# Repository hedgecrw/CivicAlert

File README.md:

# CivicAlert
Software, Firmware, and Hardware Design for the CivicAlert Gunshot Locator Project

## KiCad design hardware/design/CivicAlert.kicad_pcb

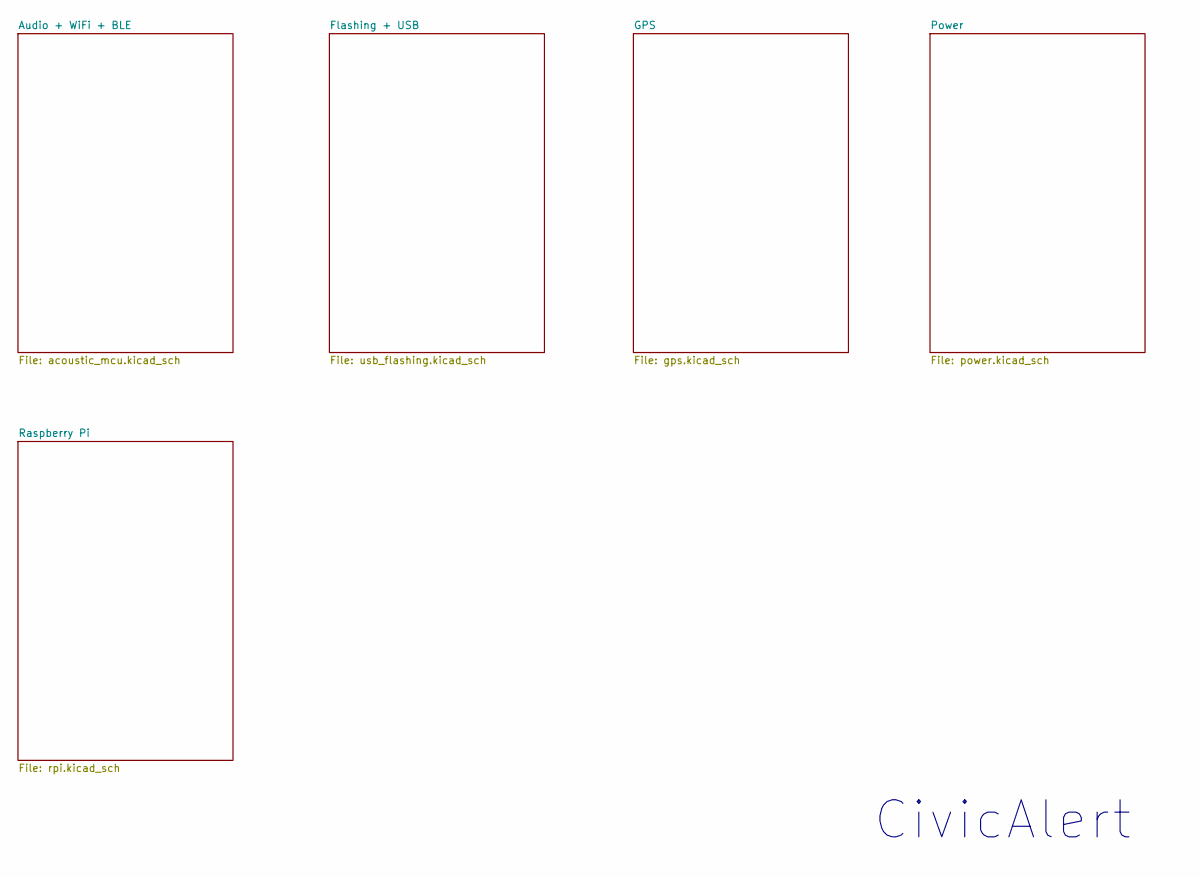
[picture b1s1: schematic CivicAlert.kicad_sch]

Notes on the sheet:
CivicAlert

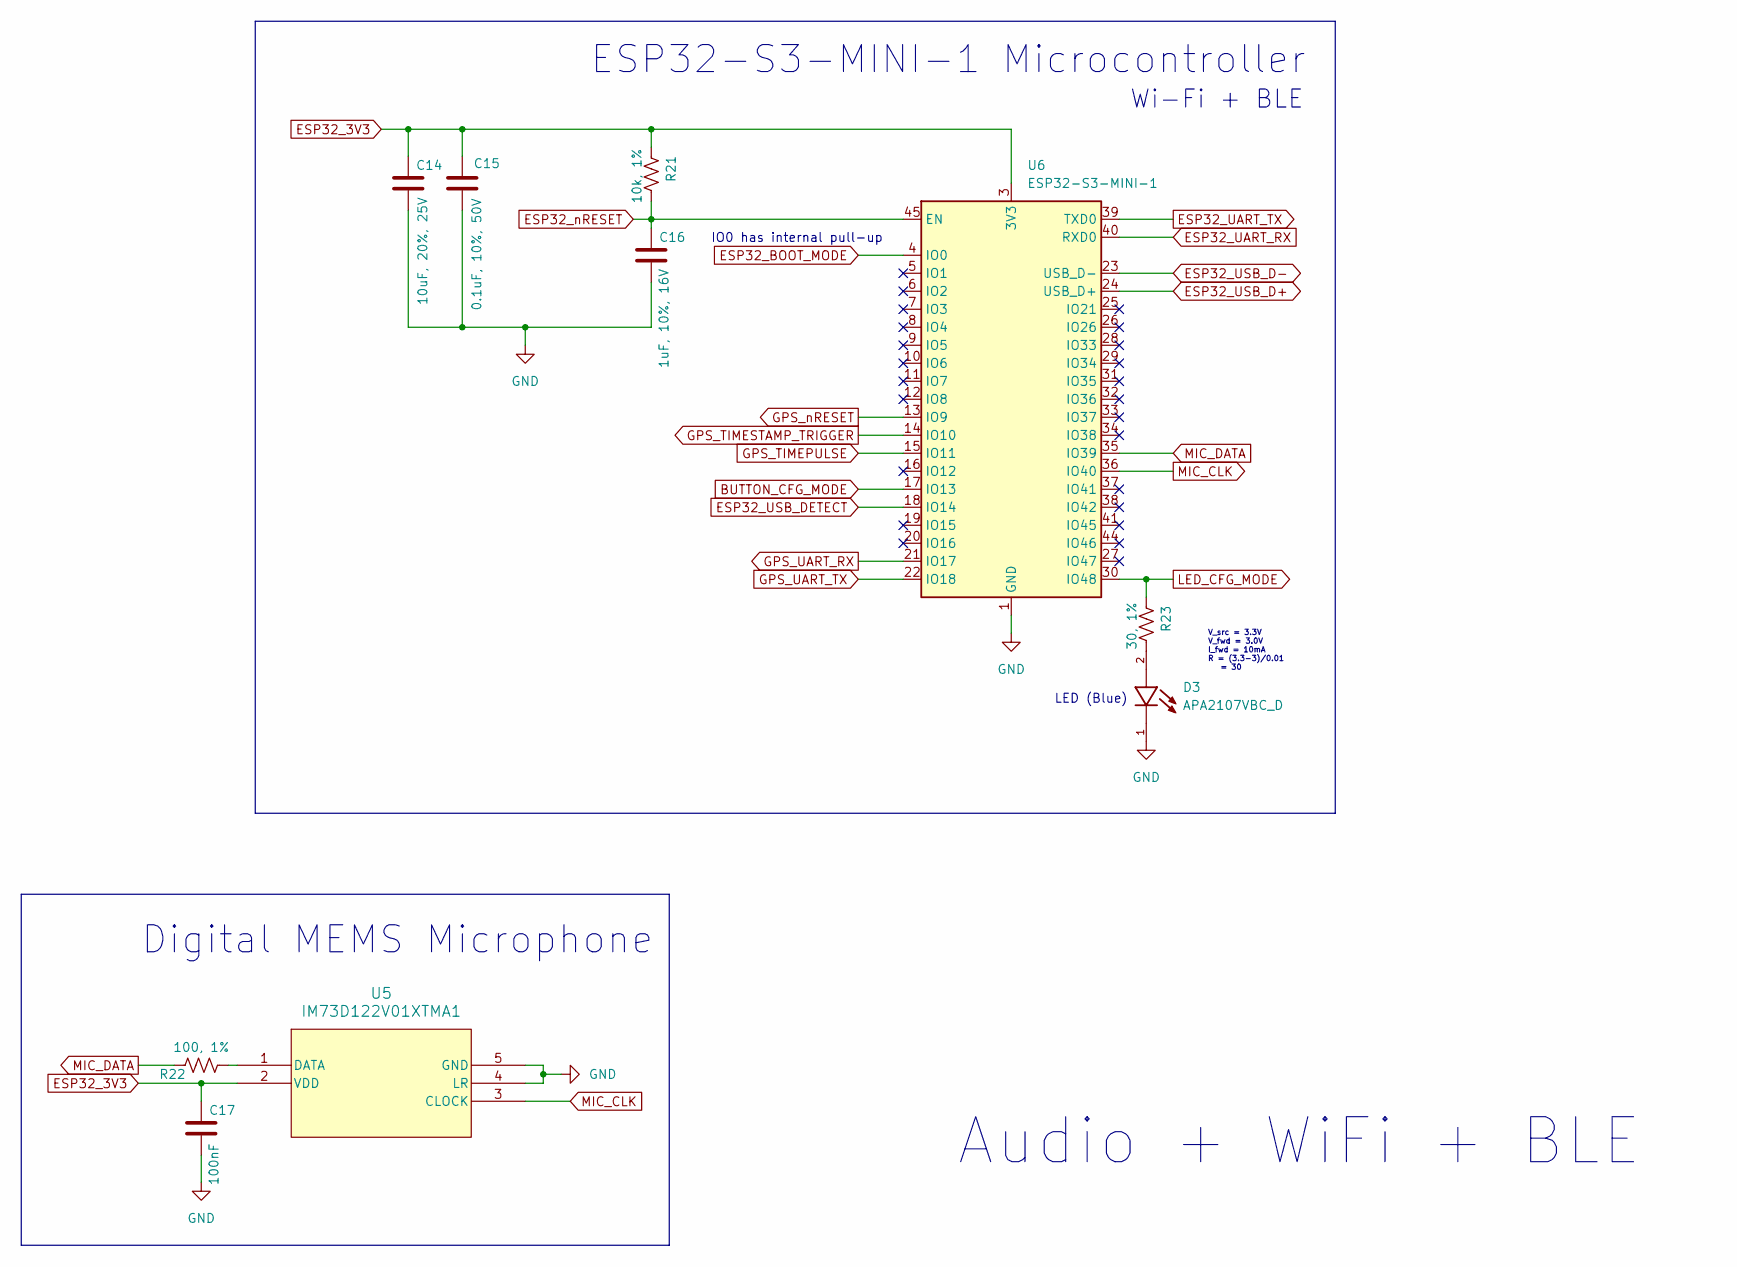
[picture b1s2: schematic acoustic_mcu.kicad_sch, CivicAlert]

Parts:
C14: 10uF, 20%, 25V; C_0805_2012Metric
C15: 0.1uF, 10%, 50V; C_0805_2012Metric
C16: 1uF, 10%, 16V; C_0805_2012Metric
C17: 100nF; C_0805_2012Metric
D3: APA2107VBC_D; LED_APA2107VBC_D; PARTREV V.5B
R21: 10k, 1%; R_0805_2012Metric
R22: 100, 1%; R_0805_2012Metric
R23: 30, 1%; R_0805_2012Metric
U5: IM73D122V01XTMA1; PG-LLGA-5-2_INF
U6: ESP32-S3-MINI-1; ESP32-S2-MINI-1

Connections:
BUTTON_CFG_MODE: U6.17 (IO13); also elsewhere on the board
ESP32_3V3: C14.1, C15.1, C17.1, R21.1, U5.2 (VDD), U6.3 (3V3); also elsewhere on the board
ESP32_BOOT_MODE: U6.4 (IO0); also elsewhere on the board
ESP32_UART_RX: U6.40 (RXD0); also elsewhere on the board
ESP32_UART_TX: U6.39 (TXD0); also elsewhere on the board
ESP32_USB_D+: U6.24 (USB_D+); also elsewhere on the board
ESP32_USB_D-: U6.23 (USB_D-); also elsewhere on the board
ESP32_USB_DETECT: U6.18 (IO14); also elsewhere on the board
ESP32_nRESET: C16.1, R21.2, U6.45 (EN); also elsewhere on the board
GND: C14.2, C15.2, C16.2, C17.2, D3.1, U5.4 (LR), U5.5 (GND), U6.1 (GND), U6.2 (GND), U6.42 (GND), U6.43 (GND), U6.46 (GND), U6.47 (GND), U6.48 (GND), U6.49 (GND), U6.50 (GND), U6.51 (GND), U6.52 (GND), U6.53 (GND), U6.54 (GND), U6.55 (GND), U6.56 (GND), U6.57 (GND), U6.58 (GND), U6.59 (GND), U6.60 (GND), U6.61 (GND), U6.62 (GND), U6.63 (GND), U6.64 (GND), U6.65 (GND); also elsewhere on the board
GPS_TIMEPULSE: U6.15 (IO11); also elsewhere on the board
GPS_TIMESTAMP_TRIGGER: U6.14 (IO10); also elsewhere on the board
GPS_UART_RX: U6.21 (IO17); also elsewhere on the board
GPS_UART_TX: U6.22 (IO18); also elsewhere on the board
GPS_nRESET: U6.13 (IO9); also elsewhere on the board
LED_CFG_MODE: R23.1, U6.30 (IO48)
MIC_CLK: U5.3 (CLOCK), U6.36 (IO40)
MIC_DATA: R22.2, U6.35 (IO39)
unnamed: D3.2, R23.2
unnamed: R22.1, U5.1 (DATA)

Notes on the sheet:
Digital MEMS Microphone
Audio + WiFi + BLE
ESP32-S3-MINI-1 Microcontroller
Wi-Fi + BLE
LED (Blue)
V_src = 3.3V V_fwd = 3.0V I_fwd = 10mA R = (3.3-3)/0.01 = 30
IO0 has internal pull-up

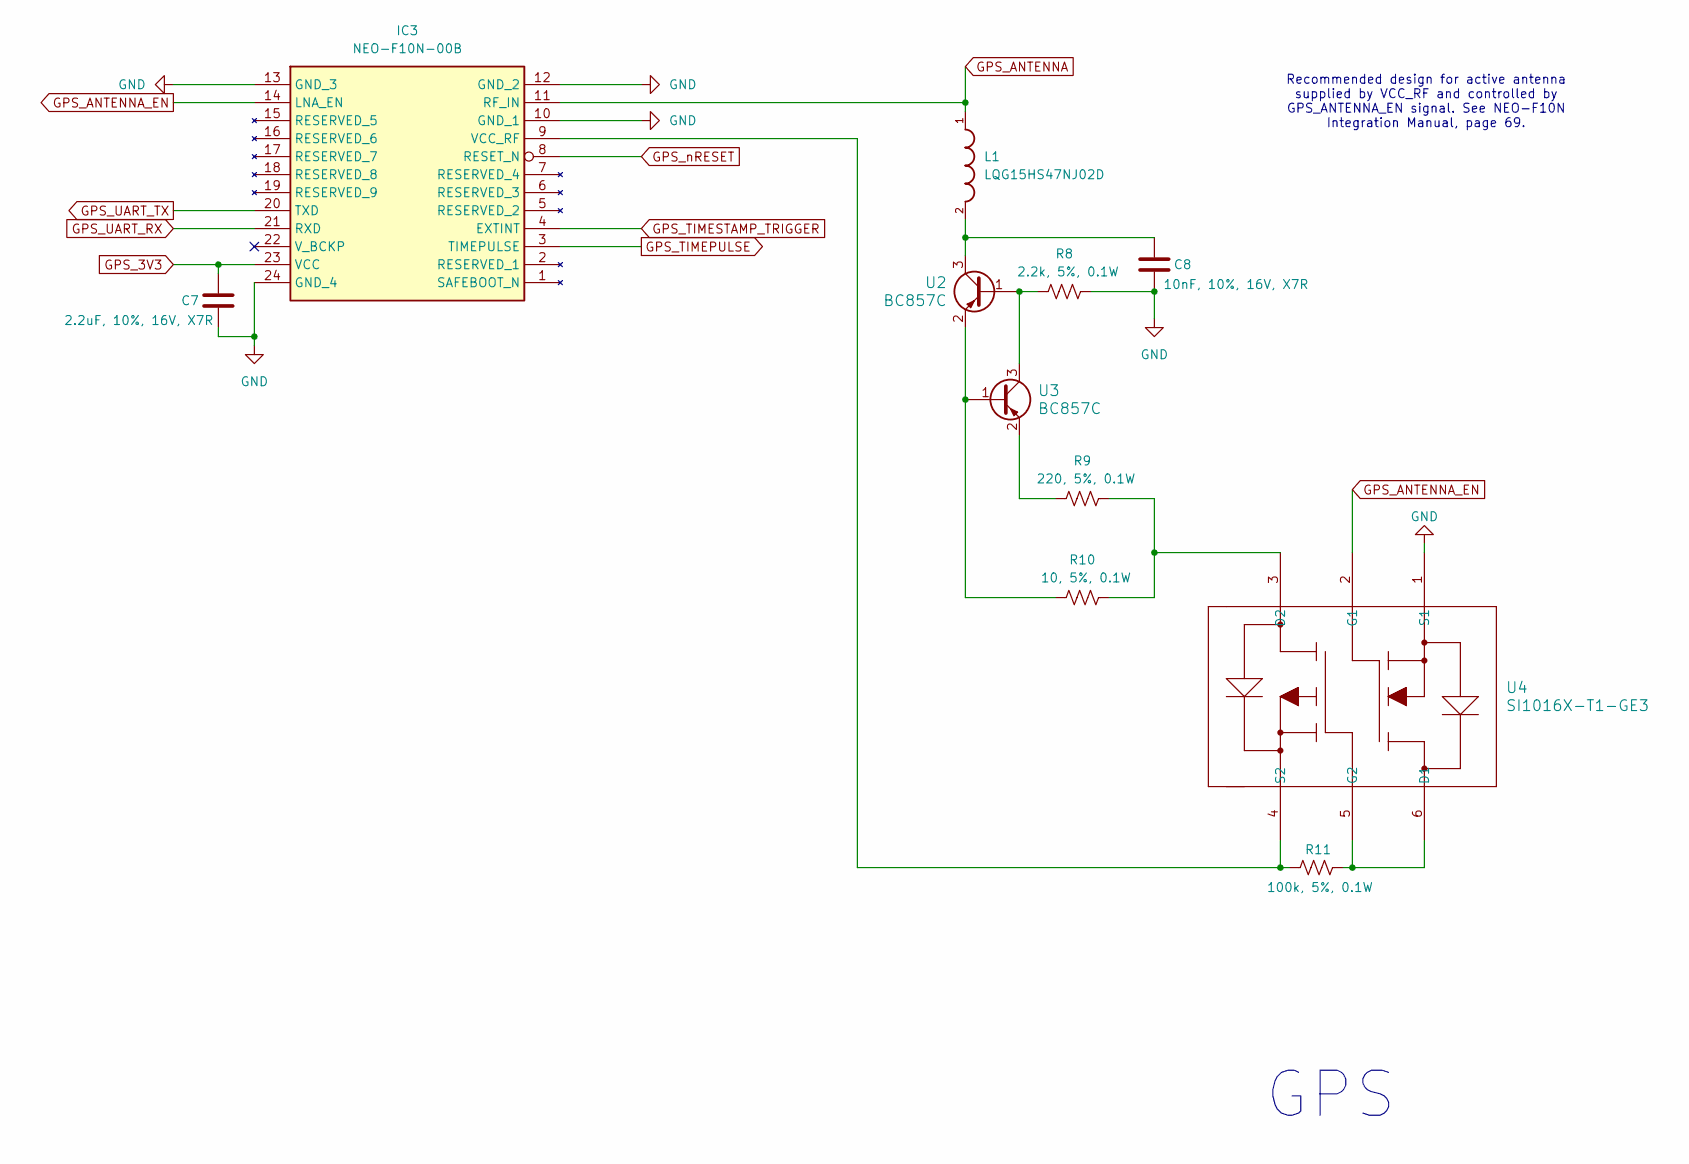
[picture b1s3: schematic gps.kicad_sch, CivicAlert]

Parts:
C7: 2.2uF, 10%, 16V, X7R; C_0805_2012Metric
C8: 10nF, 10%, 16V, X7R; C_0805_2012Metric
IC3: NEO-F10N-00B; NEOF10N00B; Mouser Part Number 377-NEO-F10N-00B
L1: LQG15HS47NJ02D; INDC1005X55N
R8: 2.2k, 5%, 0.1W; R_0805_2012Metric
R9: 220, 5%, 0.1W; R_0805_2012Metric
R10: 10, 5%, 0.1W; R_0805_2012Metric
R11: 100k, 5%, 0.1W; R_0805_2012Metric
U2, U3: BC857C; SOT-23
U4: SI1016X-T1-GE3; SOT_X-T1-GE3_VIS

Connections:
GND: C7.2, C8.2, IC3.10 (GND_1), IC3.12 (GND_2), IC3.13 (GND_3), IC3.24 (GND_4), R8.1, U4.1 (S1); also elsewhere on the board
GPS_3V3: C7.1, IC3.23 (VCC); also elsewhere on the board
GPS_ANTENNA: IC3.11 (RF_IN), L1.1
GPS_ANTENNA_EN: IC3.14 (LNA_EN), U4.2 (G1)
GPS_TIMEPULSE: IC3.3 (TIMEPULSE); also elsewhere on the board
GPS_TIMESTAMP_TRIGGER: IC3.4 (EXTINT); also elsewhere on the board
GPS_UART_RX: IC3.21 (RXD); also elsewhere on the board
GPS_UART_TX: IC3.20 (TXD); also elsewhere on the board
GPS_nRESET: IC3.8 (RESET_N); also elsewhere on the board
unnamed: IC3.9 (VCC_RF), R11.2, U4.4 (S2)
unnamed: R8.2, U2.1 (B), U3.3 (C)
unnamed: C8.1, L1.2, U2.3 (C)
unnamed: R10.2, U2.2 (E), U3.1 (B)
unnamed: R9.2, U3.2 (E)
unnamed: R11.1, U4.5 (G2), U4.6 (D1)
unnamed: R9.1, R10.1, U4.3 (D2)

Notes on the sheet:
GPS
Recommended design for active antenna supplied by VCC_RF and controlled by GPS_ANTENNA_EN signal. See NEO-F10N Integration Manual, page 69.

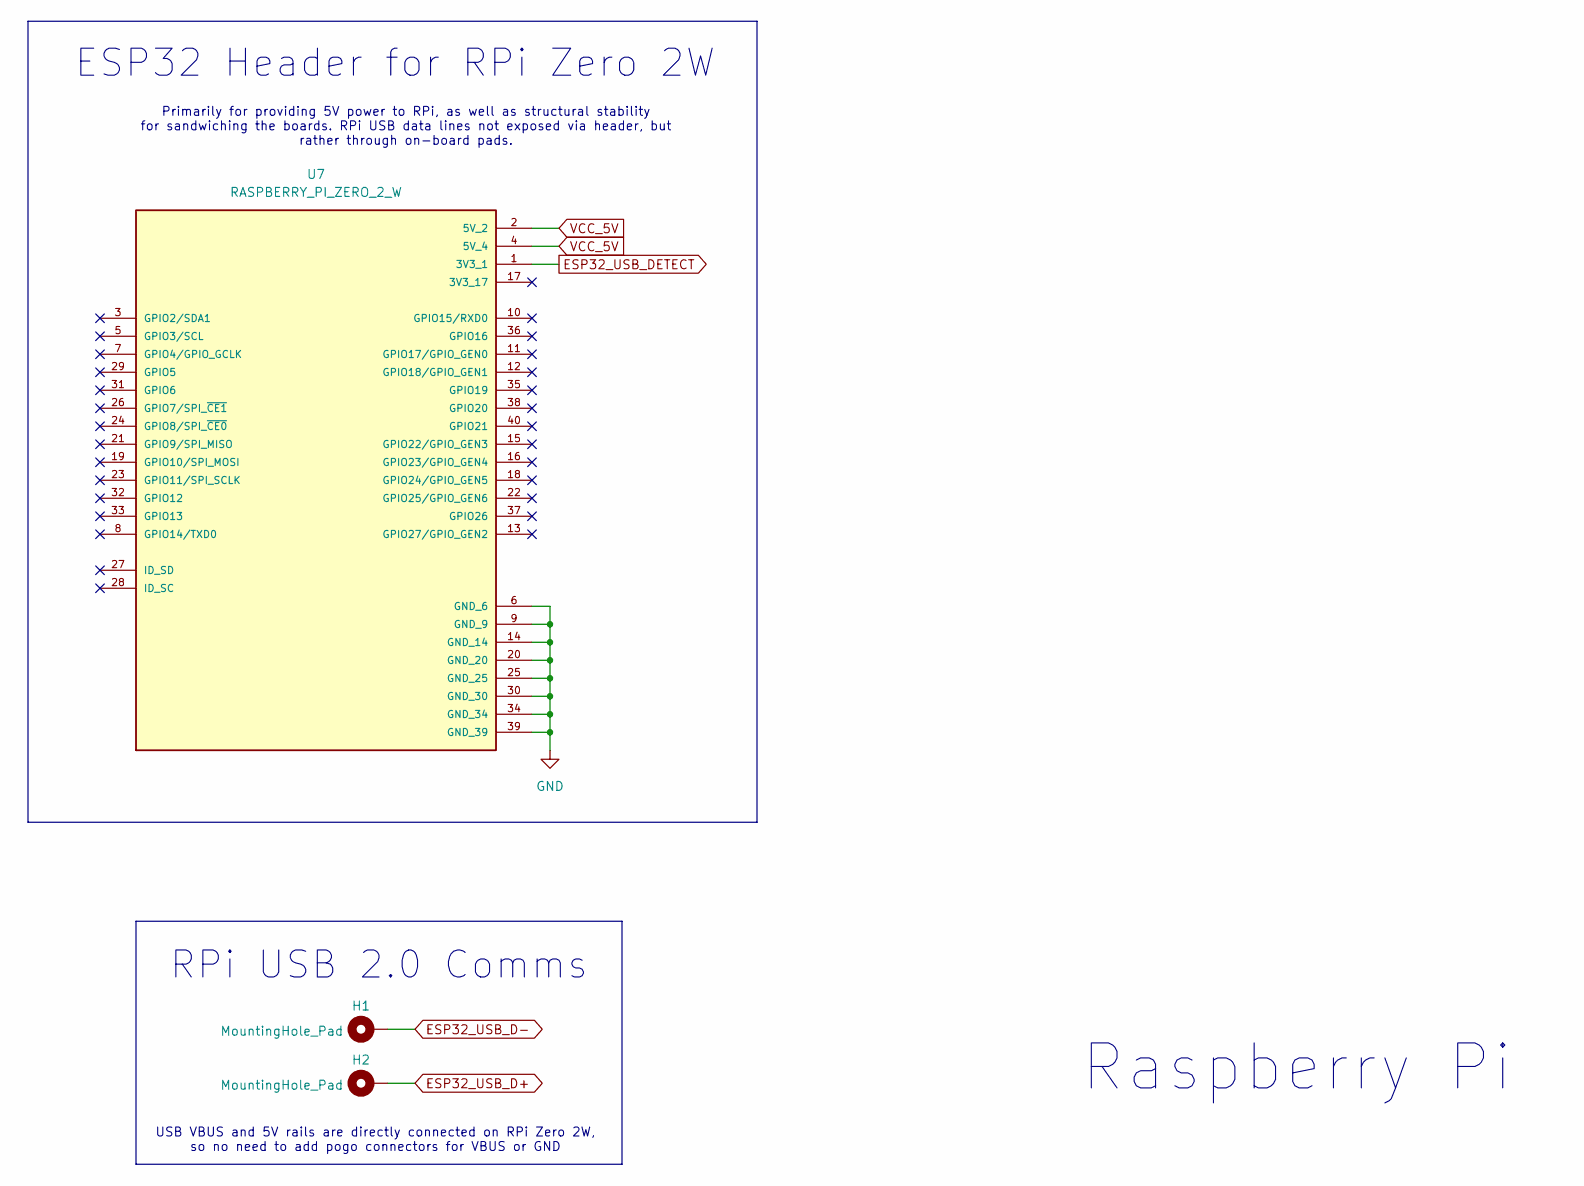
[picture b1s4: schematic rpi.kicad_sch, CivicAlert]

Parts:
H1, H2: MountingHole_Pad; PinHeader_1x01_P2.00mm_Vertical
U7: RASPBERRY_PI_ZERO_2_W; Raspberry Pi Zero 2W Header; PARTREV April 2024

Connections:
ESP32_USB_D+: H2.1; also elsewhere on the board
ESP32_USB_D-: H1.1; also elsewhere on the board
ESP32_USB_DETECT: U7.1 (3V3); also elsewhere on the board
GND: U7.6 (GND), U7.9 (GND), U7.14 (GND), U7.20 (GND), U7.25 (GND), U7.30 (GND), U7.34 (GND), U7.39 (GND); also elsewhere on the board
VCC_5V: U7.2 (5V), U7.4 (5V); also elsewhere on the board

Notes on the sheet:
Primarily for providing 5V power to RPi, as well as structural stability for sandwiching the boards. RPi USB data lines not exposed via header, but rather through on-board pads.
RPi USB 2.0 Comms
USB VBUS and 5V rails are directly connected on RPi Zero 2W, so no need to add pogo connectors for VBUS or GND
Raspberry Pi
ESP32 Header for RPi Zero 2W

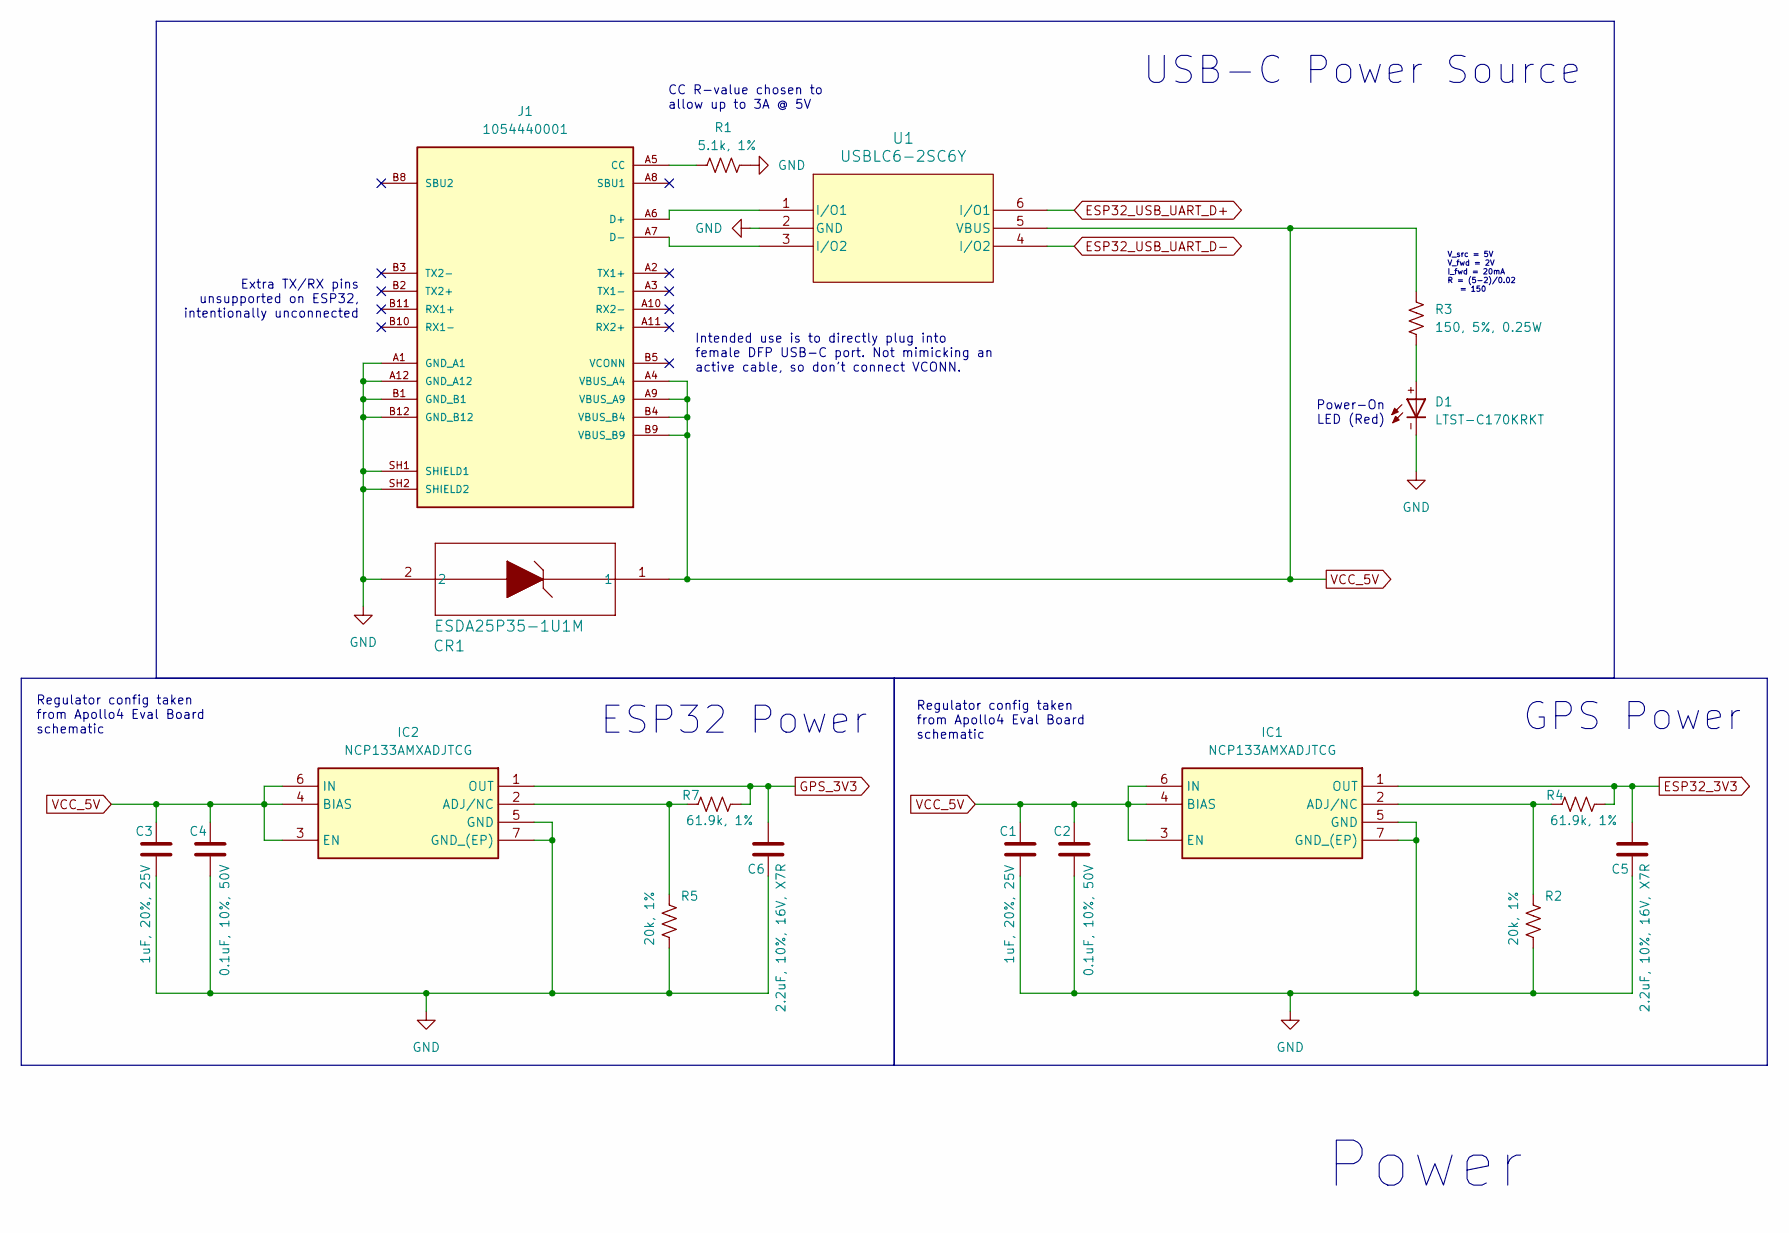
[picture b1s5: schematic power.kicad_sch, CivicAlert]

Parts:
C1, C3: 1uF, 20%, 25V; C_0805_2012Metric
C2, C4: 0.1uF, 10%, 50V; C_0805_2012Metric
C5, C6: 2.2uF, 10%, 16V, X7R; C_0805_2012Metric
CR1: ESDA25P35-1U1M; QFN1610_STM
D1: LTST-C170KRKT; DIOC200X125X110; DigiKey_Part_Number 160-1415-2-ND
IC1, IC2: NCP133AMXADJTCG; NCP133AMX110TCG; Mouser Part Number 863-NCP133AMXADJTCG
J1: 1054440001; MOLEX_1054440001; PARTREV C2; DigiKey_Part_Number WM12855-ND
R1: 5.1k, 1%; R_0805_2012Metric
R2, R5: 20k, 1%; R_0805_2012Metric
R3: 150, 5%, 0.25W; R_1206_3216Metric
R4, R7: 61.9k, 1%; R_0805_2012Metric
U1: USBLC6-2SC6Y; SOT23-6L_STM

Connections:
ESP32_3V3: C5.1, IC1.1 (OUT), R4.1; also elsewhere on the board
ESP32_USB_UART_D+: U1.6 (I/O1); also elsewhere on the board
ESP32_USB_UART_D-: U1.4 (I/O2); also elsewhere on the board
GND: C1.2, C2.2, C3.2, C4.2, C5.2, C6.2, CR1.2, D1.-, IC1.5 (GND), IC1.7 (GND_(EP)), IC2.5 (GND), IC2.7 (GND_(EP)), J1.A1 (GND_A1), J1.A12 (GND_A12), J1.B1 (GND_B1), J1.B12 (GND_B12), J1.SH1 (SHIELD1), J1.SH2 (SHIELD2), R1.1, R2.2, R5.2, U1.2 (GND); also elsewhere on the board
GPS_3V3: C6.1, IC2.1 (OUT), R7.1; also elsewhere on the board
unnamed: D1.+, R3.2
unnamed: IC1.2 (ADJ/NC), R2.1, R4.2
unnamed: IC2.2 (ADJ/NC), R5.1, R7.2
unnamed: J1.A5 (CC), R1.2
unnamed: J1.A6 (D+), U1.1 (I/O1)
unnamed: J1.A7 (D-), U1.3 (I/O2)
VCC_5V: C1.1, C2.1, C3.1, C4.1, CR1.1, IC1.3 (EN), IC1.4 (BIAS), IC1.6 (IN), IC2.3 (EN), IC2.4 (BIAS), IC2.6 (IN), J1.A4 (VBUS_A4), J1.A9 (VBUS_A9), J1.B4 (VBUS_B4), J1.B9 (VBUS_B9), R3.1, U1.5 (VBUS); also elsewhere on the board

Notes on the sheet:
Intended use is to directly plug into female DFP USB-C port. Not mimicking an active cable, so don't connect VCONN.
Regulator config taken from Apollo4 Eval Board schematic
Power
CC R-value chosen to allow up to 3A @ 5V
GPS Power
ESP32 Power
V_src = 5V V_fwd = 2V I_fwd = 20mA R = (5-2)/0.02 = 150
Extra TX/RX pins unsupported on ESP32, intentionally unconnected
USB-C Power Source
Power-On LED (Red)

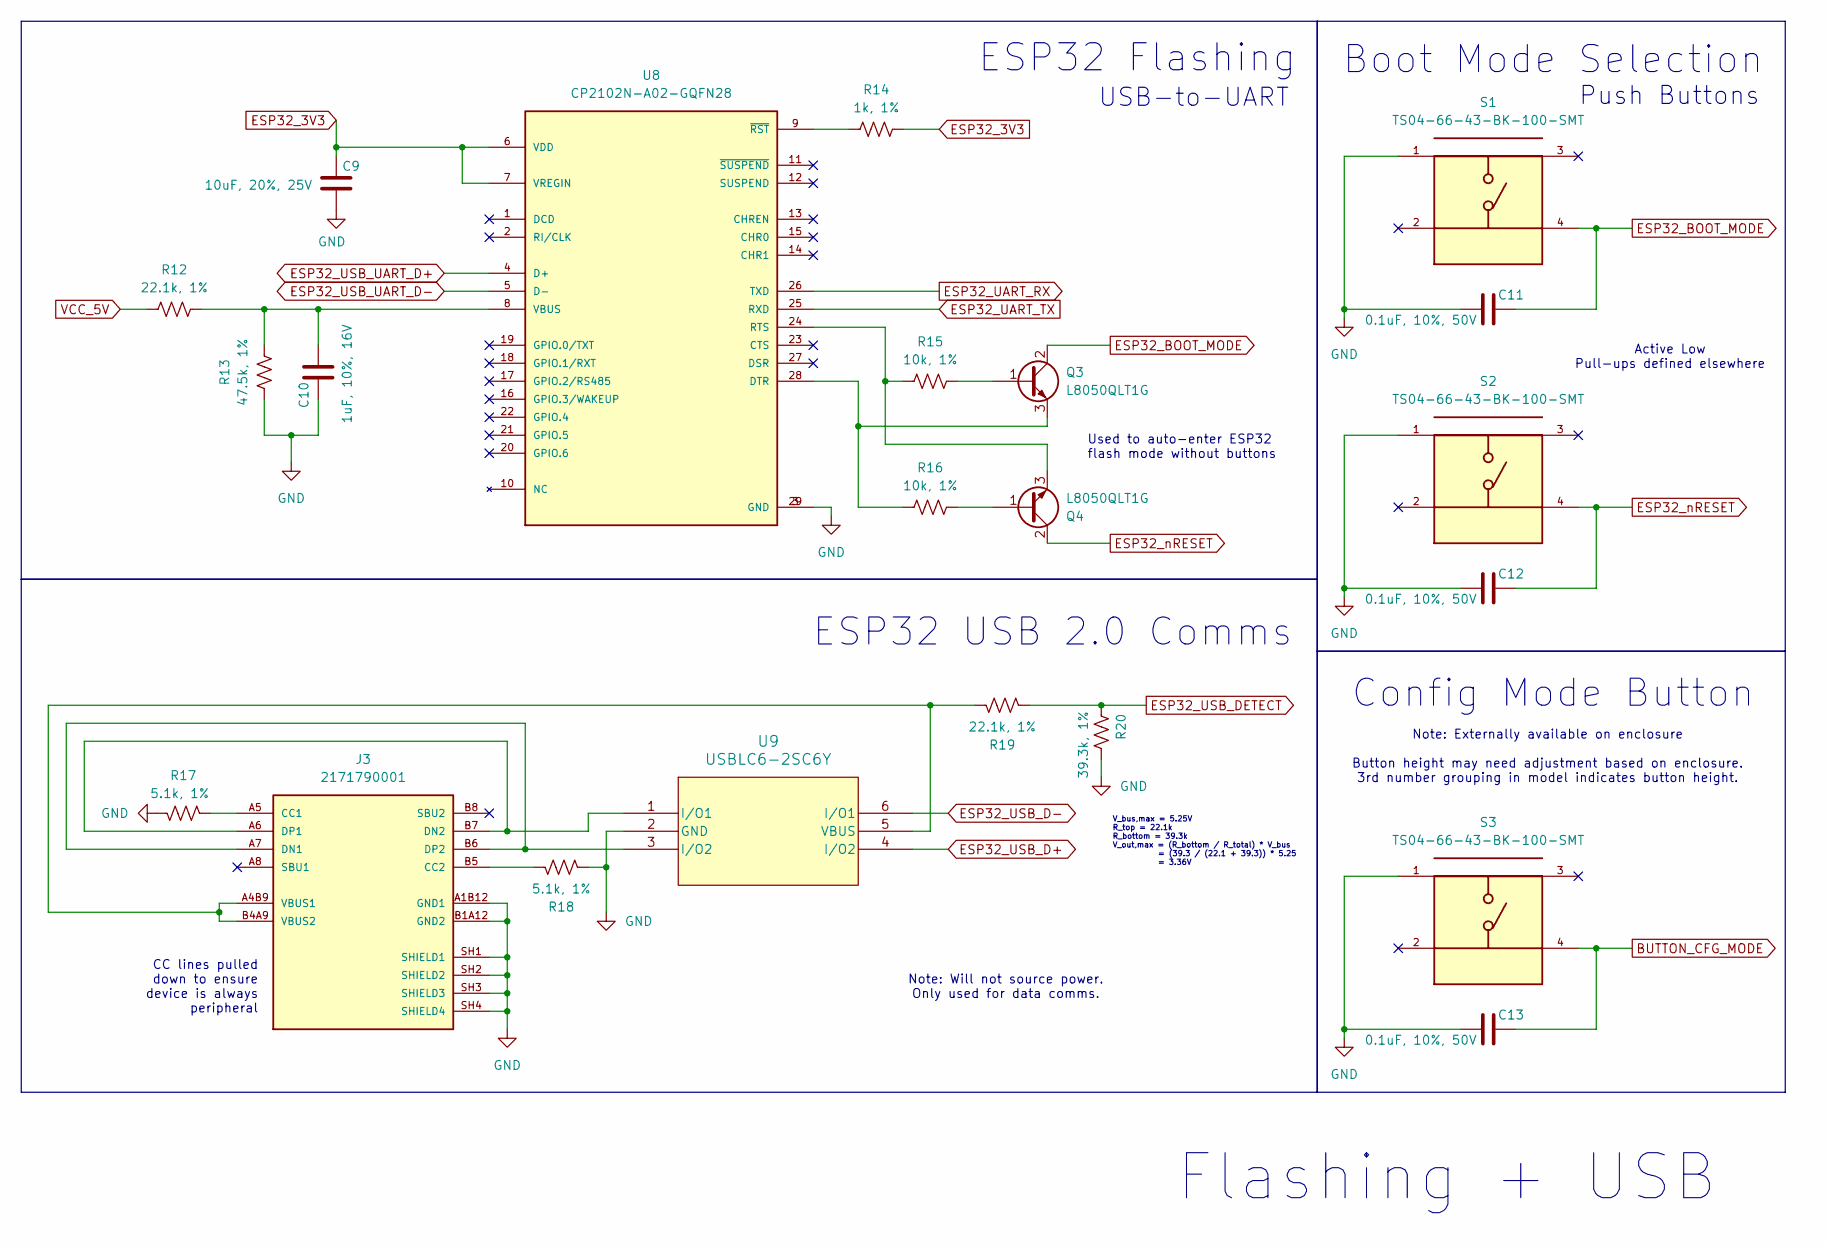
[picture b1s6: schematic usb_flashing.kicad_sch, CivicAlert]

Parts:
C9: 10uF, 20%, 25V; C_0805_2012Metric
C10: 1uF, 10%, 16V; C_0805_2012Metric
C11, C12, C13: 0.1uF, 10%, 50V; C_0805_2012Metric
J3: 2171790001; MOLEX_2171790001; PARTREV A1; DigiKey_Part_Number 900-2171790001TR-ND
Q3, Q4: L8050QLT1G
R12, R19: 22.1k, 1%; R_0805_2012Metric
R13: 47.5k, 1%; R_0805_2012Metric
R14: 1k, 1%; R_0805_2012Metric
R15, R16: 10k, 1%; R_0805_2012Metric
R17, R18: 5.1k, 1%; R_0805_2012Metric
R20: 39.3k, 1%; R_0805_2012Metric
S1, S2, S3: TS04-66-43-BK-100-SMT; SW_TS04-66-43-BK-100-SMT; PARTREV 1.0
U8: CP2102N-A02-GQFN28; QFN50P500X500X80-29N; PARTREV 1.5; DigiKey_Part_Number 336-5889-ND
U9: USBLC6-2SC6Y; SOT23-6L_STM

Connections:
BUTTON_CFG_MODE: C13.1, S3.4; also elsewhere on the board
ESP32_3V3: C9.1, R14.1, U8.6 (VDD), U8.7 (VREGIN); also elsewhere on the board
ESP32_BOOT_MODE: C11.1, Q3.2 (C), S1.4; also elsewhere on the board
ESP32_UART_RX: U8.26 (TXD); also elsewhere on the board
ESP32_UART_TX: U8.25 (RXD); also elsewhere on the board
ESP32_USB_D+: U9.4 (I/O2); also elsewhere on the board
ESP32_USB_D-: U9.6 (I/O1); also elsewhere on the board
ESP32_USB_DETECT: R19.1, R20.1; also elsewhere on the board
ESP32_USB_UART_D+: U8.4 (D+); also elsewhere on the board
ESP32_USB_UART_D-: U8.5 (D-); also elsewhere on the board
ESP32_nRESET: C12.1, Q4.2 (C), S2.4; also elsewhere on the board
GND: C9.2, C10.1, C11.2, C12.2, C13.2, J3.A1B12 (GND1), J3.B1A12 (GND2), J3.SH1 (SHIELD1), J3.SH2 (SHIELD2), J3.SH3 (SHIELD3), J3.SH4 (SHIELD4), R13.2, R17.1, R18.1, R20.2, S1.1, S2.1, S3.1, U8.3 (GND), U8.29 (GND), U9.2 (GND); also elsewhere on the board
unnamed: J3.A5 (CC1), R17.2
unnamed: J3.B5 (CC2), R18.2
unnamed: J3.A7 (DN1), J3.B6 (DP2), U9.3 (I/O2)
unnamed: J3.A6 (DP1), J3.B7 (DN2), U9.1 (I/O1)
unnamed: J3.A4B9 (VBUS1), J3.B4A9 (VBUS2), R19.2, U9.5 (VBUS)
unnamed: Q3.1 (B), R15.1
unnamed: Q3.3 (E), R16.2, U8.28 (DTR)
unnamed: Q4.1 (B), R16.1
unnamed: Q4.3 (E), R15.2, U8.24 (RTS)
unnamed: C10.2, R12.1, R13.1, U8.8 (VBUS)
unnamed: R14.2, U8.9 (~RST)
VCC_5V: R12.2; also elsewhere on the board

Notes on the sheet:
Active Low Pull-ups defined elsewhere
CC lines pulled down to ensure device is always peripheral
Note: Will not source power. Only used for data comms.
V_bus,max = 5.25V R_top = 22.1k R_bottom = 39.3k V_out,max = (R_bottom / R_total) * V_bus = (39.3 / (22.1 + 39.3)) * 5.25 = 3.36V
Note: Externally available on enclosure Button height may need adjustment based on enclosure. 3rd number grouping in model indicates button height.
Push Buttons
Flashing + USB
Used to auto-enter ESP32 flash mode without buttons
USB-to-UART
Boot Mode Selection
Config Mode Button
ESP32 Flashing
ESP32 USB 2.0 Comms

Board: 4 copper layers, 68 parts (0 on the bottom side), 50 nets, no tracks yet.

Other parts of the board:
MountingHole: MountingHole_2.7mm
MountingHole#2, MountingHole#3, MountingHole#4: MountingHole_2.7mm

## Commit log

2025-01-08 Update gitignore
2025-01-08 Start work on layout
